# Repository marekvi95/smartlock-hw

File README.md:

# smartlock-hw

This repository contains PCB design for the **smartlock**. This project started as the final thesis at the Brno University of Technology. The aim of this project is to create a smartlock that that could be used for securing the objects.

Project is created with KiCAD version 6.0.0 nightly builds. KiCAD can be downloaded here https://kicad-pcb.org/download/

## Smartlock

Battery powered smartlock using IoT networks and NFC technology for the user authentication. Firmware source code is in this repo: https://github.com/marekvi95/smartlock-fw

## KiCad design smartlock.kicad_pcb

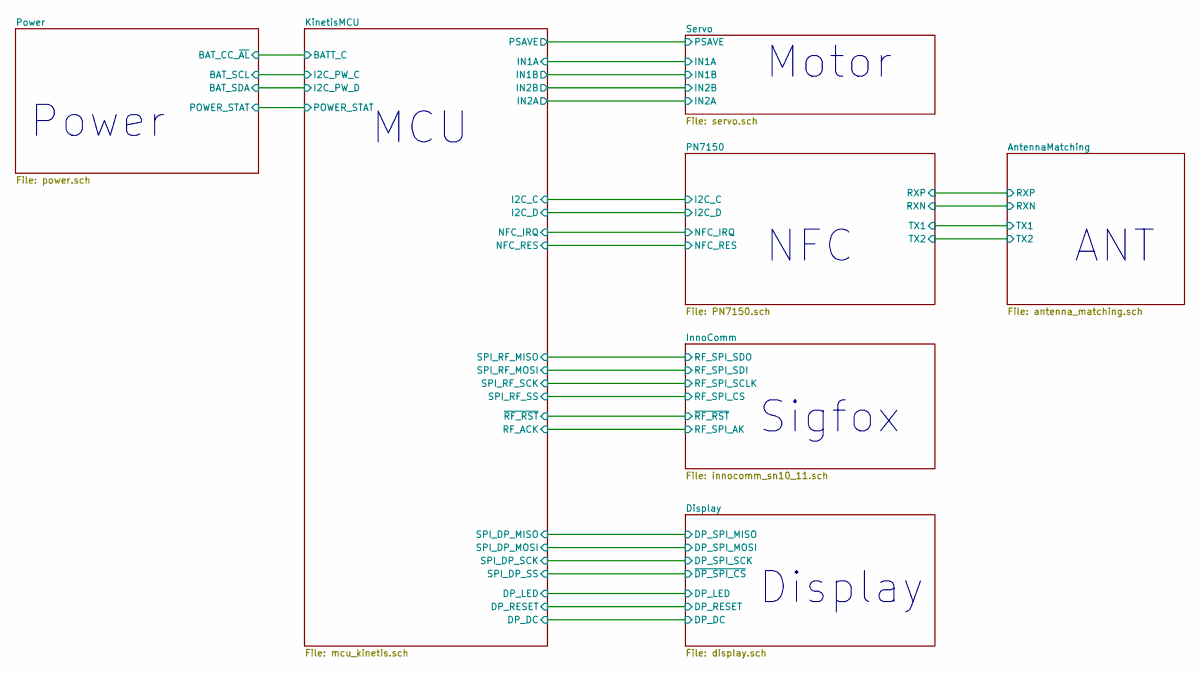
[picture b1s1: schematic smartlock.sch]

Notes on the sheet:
NFC
ANT
Sigfox
MCU
Power
Display
Motor

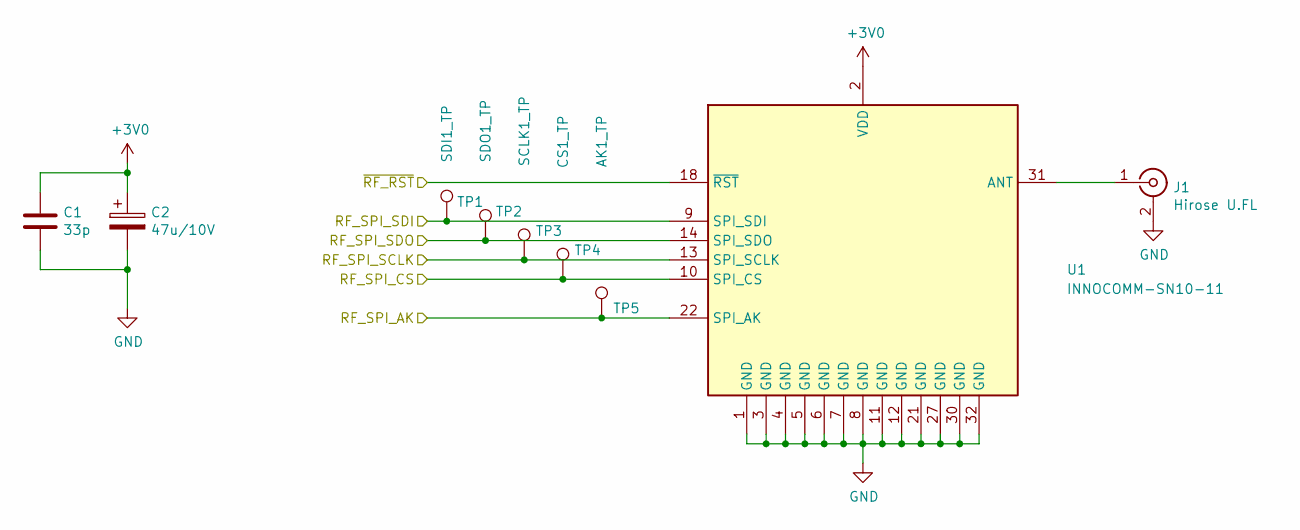
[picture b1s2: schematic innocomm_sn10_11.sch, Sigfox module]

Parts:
C1: 33p; C_0805_2012Metric
C2: 47u/10V; CP_EIA-3528-21_Kemet-B
J1: Hirose U.FL; U.FL_Hirose_U.FL-R-SMT-1_Vertical
TP1: SDI1_TP; TestPoint_Loop_D2.50mm_Drill1.0mm_LowProfile
TP2: SDO1_TP; TestPoint_Loop_D2.50mm_Drill1.0mm_LowProfile
TP3: SCLK1_TP; TestPoint_Loop_D2.50mm_Drill1.0mm_LowProfile
TP4: CS1_TP; TestPoint_Loop_D2.50mm_Drill1.0mm_LowProfile
TP5: AK1_TP; TestPoint_Loop_D2.50mm_Drill1.0mm_LowProfile
U1: INNOCOMM-SN10-11; InnoCommSN10-11

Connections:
+3V0: C1.1, C2.1, U1.2 (VDD); also elsewhere on the board
/InnoComm/RF_SPI_CS: TP4.1, U1.10 (SPI_CS); also elsewhere on the board
/InnoComm/RF_SPI_SCLK: TP3.1, U1.13 (SPI_SCLK); also elsewhere on the board
/InnoComm/RF_SPI_SDI: TP1.1, U1.9 (SPI_SDI); also elsewhere on the board
/InnoComm/RF_SPI_SDO: TP2.1, U1.14 (SPI_SDO); also elsewhere on the board
/InnoComm/~RF_RST: U1.18 (~RST); also elsewhere on the board
/KinetisMCU/RF_ACK: TP5.1, U1.22 (SPI_AK); also elsewhere on the board
GND: C1.2, C2.2, J1.2 (Ext), U1.1 (GND), U1.3 (GND), U1.4 (GND), U1.5 (GND), U1.6 (GND), U1.7 (GND), U1.8 (GND), U1.11 (GND), U1.12 (GND), U1.21 (GND), U1.27 (GND), U1.30 (GND), U1.32 (GND); also elsewhere on the board
unnamed: J1.1 (In), U1.31 (ANT)

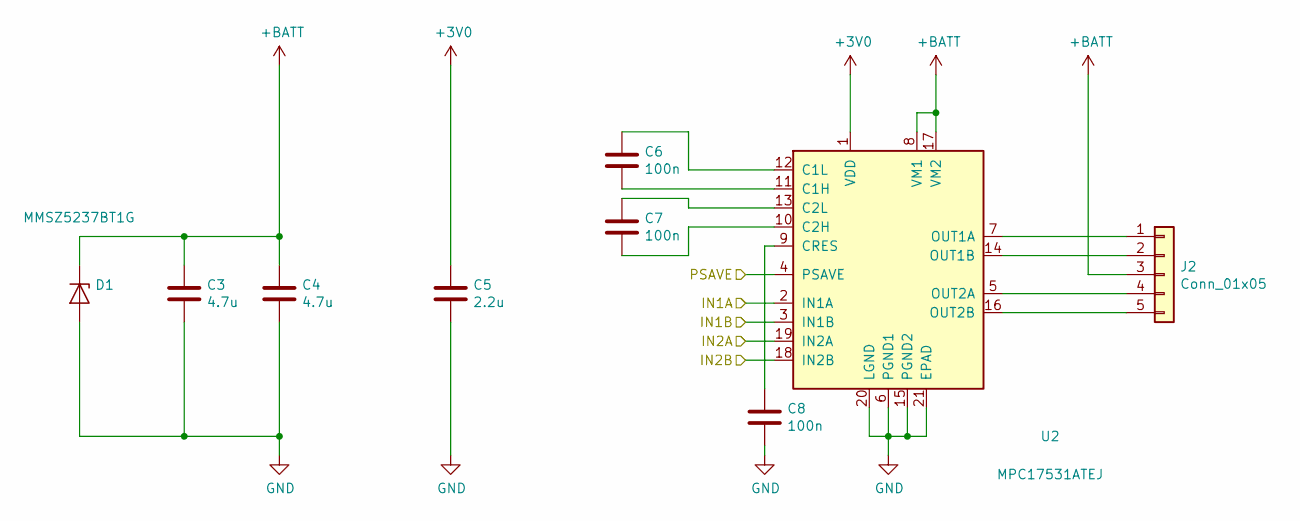
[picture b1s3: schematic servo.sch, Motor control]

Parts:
C3, C4: 4.7u; C_0805_2012Metric
C5: 2.2u; C_0805_2012Metric
C6, C7, C8: 100n; C_0805_2012Metric
D1: MMSZ5237BT1G; D_SOD-123
J2: Conn_01x05; PinHeader_1x05_P2.54mm_Vertical
U2: MPC17531ATEJ; HTSSOP-20-1EP_4.4x6.5mm_P0.65mm_EP3.4x6.5mm_ThermalVias

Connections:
+3V0: C5.1, U2.1 (VDD); also elsewhere on the board
+BATT: C3.1, C4.1, D1.1 (K), J2.3, U2.8 (VM1), U2.17 (VM2); also elsewhere on the board
/KinetisMCU/IN1A: U2.2 (IN1A); also elsewhere on the board
/KinetisMCU/IN1B: U2.3 (IN1B); also elsewhere on the board
/KinetisMCU/IN2A: U2.19 (IN2A); also elsewhere on the board
/KinetisMCU/IN2B: U2.18 (IN2B); also elsewhere on the board
/KinetisMCU/PSAVE: U2.4 (PSAVE); also elsewhere on the board
GND: C3.2, C4.2, C5.2, C8.2, D1.2 (A), U2.6 (PGND1), U2.15 (PGND2), U2.20 (LGND), U2.21 (EPAD); also elsewhere on the board
unnamed: C6.1, U2.12 (C1L)
unnamed: C6.2, U2.11 (C1H)
unnamed: C7.1, U2.13 (C2L)
unnamed: C7.2, U2.10 (C2H)
unnamed: C8.1, U2.9 (CRES)
unnamed: J2.1, U2.7 (OUT1A)
unnamed: J2.2, U2.14 (OUT1B)
unnamed: J2.4, U2.5 (OUT2A)
unnamed: J2.5, U2.16 (OUT2B)

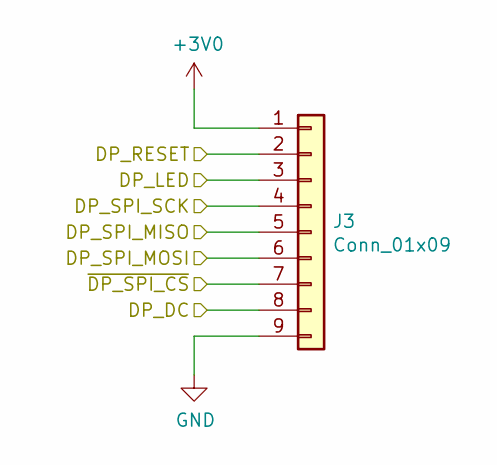
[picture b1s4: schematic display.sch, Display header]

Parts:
J3: Conn_01x09; PinHeader_1x09_P2.54mm_Vertical

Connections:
+3V0: J3.1; also elsewhere on the board
/Display/DP_DC: J3.8; also elsewhere on the board
/Display/DP_LED: J3.3; also elsewhere on the board
/Display/DP_RESET: J3.2; also elsewhere on the board
/Display/DP_SPI_MISO: J3.5; also elsewhere on the board
/Display/DP_SPI_MOSI: J3.6; also elsewhere on the board
/Display/DP_SPI_SCK: J3.4; also elsewhere on the board
/KinetisMCU/SPI_DP_SS: J3.7; also elsewhere on the board
GND: J3.9; also elsewhere on the board

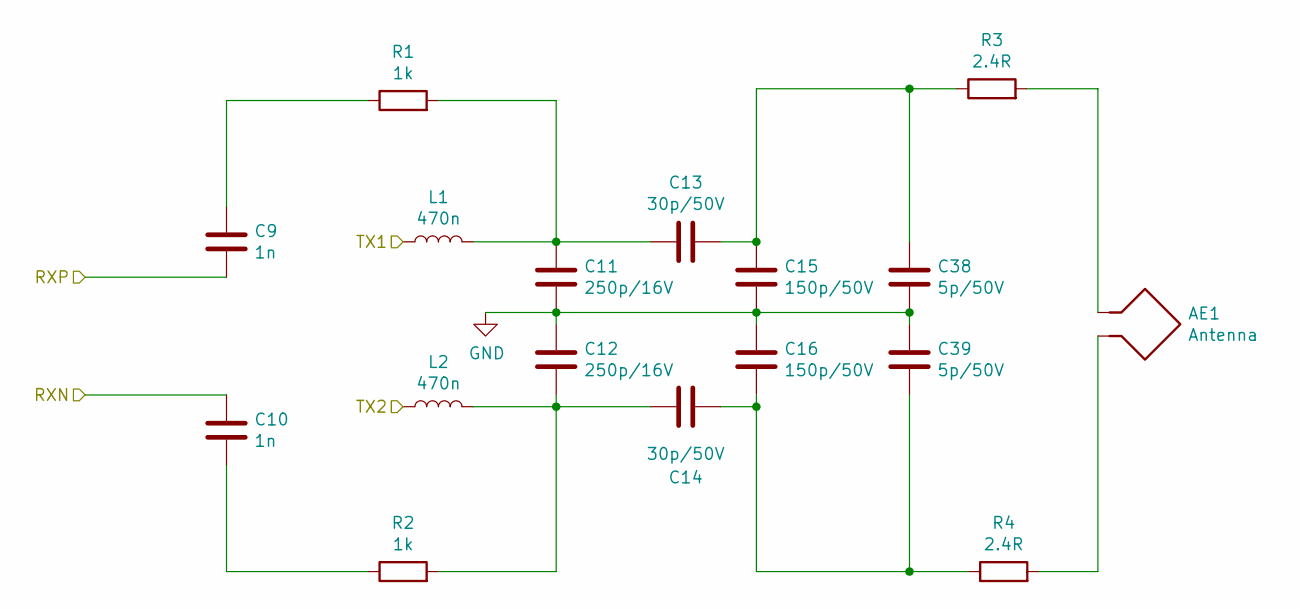
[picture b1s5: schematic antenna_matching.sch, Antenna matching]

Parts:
AE1: Antenna; nfc_40_75
C9, C10: 1n; C_0805_2012Metric
C11, C12: 250p/16V; C_0805_2012Metric
C13, C14: 30p/50V; C_0805_2012Metric
C15, C16: 150p/50V; C_0805_2012Metric
C38, C39: 5p/50V; C_0805_2012Metric
L1, L2: 470n; L_0805_2012Metric
R1, R2: 1k; R_0805_2012Metric
R3, R4: 2.4R; R_0805_2012Metric

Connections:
/AntennaMatching/RXN: C10.1; also elsewhere on the board
/AntennaMatching/RXP: C9.2; also elsewhere on the board
/AntennaMatching/TX1: L1.1; also elsewhere on the board
/AntennaMatching/TX2: L2.1; also elsewhere on the board
GND: C11.2, C12.1, C15.2, C16.1, C38.2, C39.1; also elsewhere on the board
unnamed: AE1.1, R3.2
unnamed: AE1.2, R4.2
unnamed: C9.1, R1.1
unnamed: C10.2, R2.1
unnamed: C11.1, C13.1, L1.2, R1.2
unnamed: C12.2, C14.1, L2.2, R2.2
unnamed: C13.2, C15.1, C38.1, R3.1
unnamed: C14.2, C16.2, C39.2, R4.1

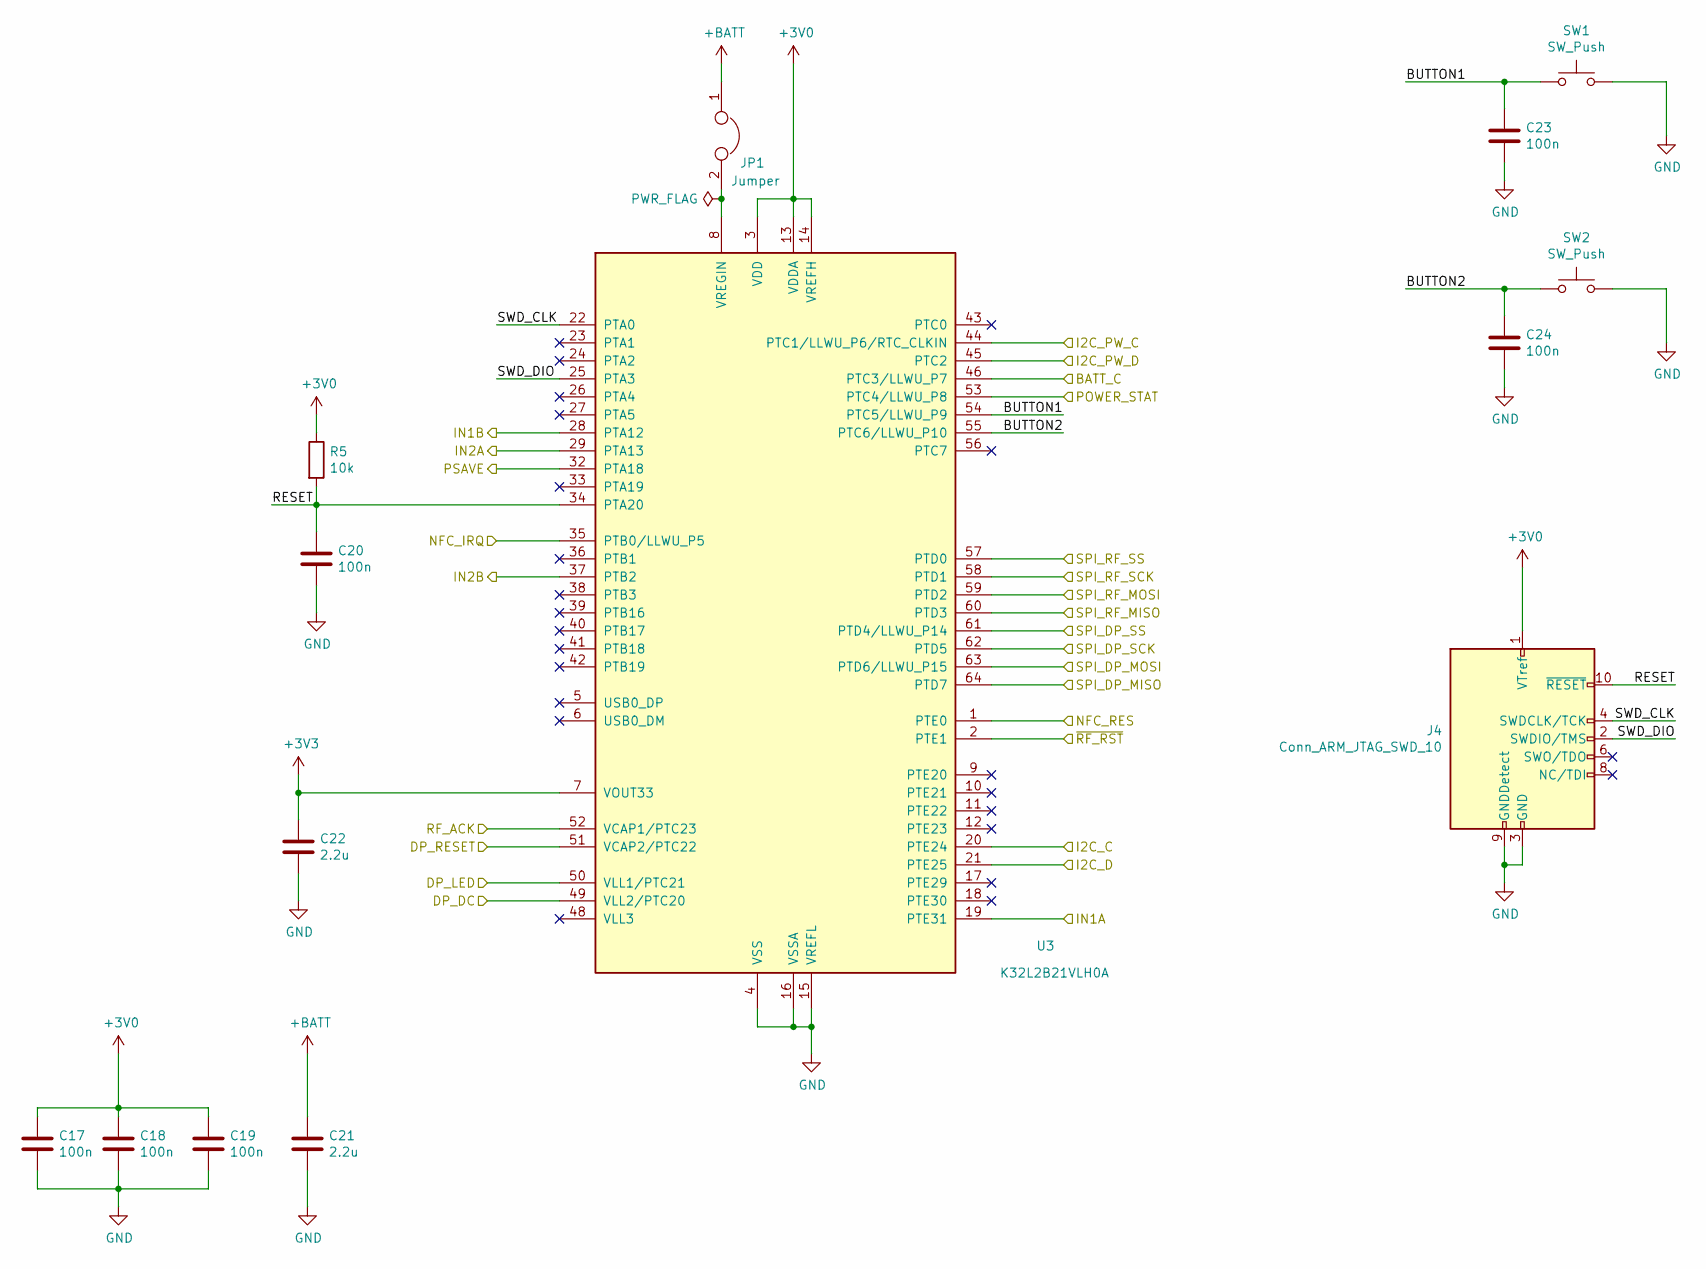
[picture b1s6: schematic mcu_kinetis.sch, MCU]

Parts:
C17, C18, C19, C20, C23, C24: 100n; C_0805_2012Metric
C21, C22: 2.2u; C_0805_2012Metric
J4: Conn_ARM_JTAG_SWD_10; PinHeader_2x05_P1.27mm_Vertical
JP1: Jumper; SolderJumper-2_P1.3mm_Bridged_Pad1.0x1.5mm
R5: 10k; R_0805_2012Metric
SW1, SW2: SW_Push; PinHeader_1x02_P1.27mm_Vertical
U3: K32L2B21VLH0A; LQFP-64_10x10mm_P0.5mm

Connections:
+3V0: C17.1, C18.1, C19.1, J4.1 (VTref), R5.1, U3.3 (VDD), U3.13 (VDDA), U3.14 (VREFH), U3.30 (VDD); also elsewhere on the board
+3V3: C22.1, U3.7 (VOUT33)
+BATT: C21.1, JP1.1; also elsewhere on the board
/Display/DP_DC: U3.49 (VLL2/PTC20); also elsewhere on the board
/Display/DP_LED: U3.50 (VLL1/PTC21); also elsewhere on the board
/Display/DP_RESET: U3.51 (VCAP2/PTC22); also elsewhere on the board
/Display/DP_SPI_MISO: U3.64 (PTD7); also elsewhere on the board
/Display/DP_SPI_MOSI: U3.63 (PTD6/LLWU_P15); also elsewhere on the board
/Display/DP_SPI_SCK: U3.62 (PTD5); also elsewhere on the board
/InnoComm/RF_SPI_CS: U3.57 (PTD0); also elsewhere on the board
/InnoComm/RF_SPI_SCLK: U3.58 (PTD1); also elsewhere on the board
/InnoComm/RF_SPI_SDI: U3.59 (PTD2); also elsewhere on the board
/InnoComm/RF_SPI_SDO: U3.60 (PTD3); also elsewhere on the board
/InnoComm/~RF_RST: U3.2 (PTE1); also elsewhere on the board
/KinetisMCU/BATT_C: U3.46 (PTC3/LLWU_P7); also elsewhere on the board
/KinetisMCU/BUTTON1: C23.1, SW1.1, U3.54 (PTC5/LLWU_P9)
/KinetisMCU/BUTTON2: C24.1, SW2.1, U3.55 (PTC6/LLWU_P10)
/KinetisMCU/I2C_C: U3.20 (PTE24); also elsewhere on the board
/KinetisMCU/I2C_D: U3.21 (PTE25); also elsewhere on the board
/KinetisMCU/IN1A: U3.19 (PTE31); also elsewhere on the board
/KinetisMCU/IN1B: U3.28 (PTA12); also elsewhere on the board
/KinetisMCU/IN2A: U3.29 (PTA13); also elsewhere on the board
/KinetisMCU/IN2B: U3.37 (PTB2); also elsewhere on the board
/KinetisMCU/NFC_IRQ: U3.35 (PTB0/LLWU_P5); also elsewhere on the board
/KinetisMCU/NFC_RES: U3.1 (PTE0); also elsewhere on the board
/KinetisMCU/POWER_STAT: U3.53 (PTC4/LLWU_P8); also elsewhere on the board
/KinetisMCU/PSAVE: U3.32 (PTA18); also elsewhere on the board
/KinetisMCU/RESET: C20.1, J4.10 (~RESET~), R5.2, U3.34 (PTA20)
/KinetisMCU/RF_ACK: U3.52 (VCAP1/PTC23); also elsewhere on the board
/KinetisMCU/SPI_DP_SS: U3.61 (PTD4/LLWU_P14); also elsewhere on the board
/KinetisMCU/SWD_CLK: J4.4 (SWDCLK/TCK), U3.22 (PTA0)
/KinetisMCU/SWD_DIO: J4.2 (SWDIO/TMS), U3.25 (PTA3)
/Power/BAT_SCL: U3.44 (PTC1/LLWU_P6/RTC_CLKIN); also elsewhere on the board
/Power/BAT_SDA: U3.45 (PTC2); also elsewhere on the board
GND: C17.2, C18.2, C19.2, C20.2, C21.2, C22.2, C23.2, C24.2, J4.3 (GND), J4.5 (GND), J4.9 (GNDDetect), SW1.2, SW2.2, U3.4 (VSS), U3.15 (VREFL), U3.16 (VSSA), U3.31 (VSS), U3.47 (VSS); also elsewhere on the board
unnamed: JP1.2, U3.8 (VREGIN)

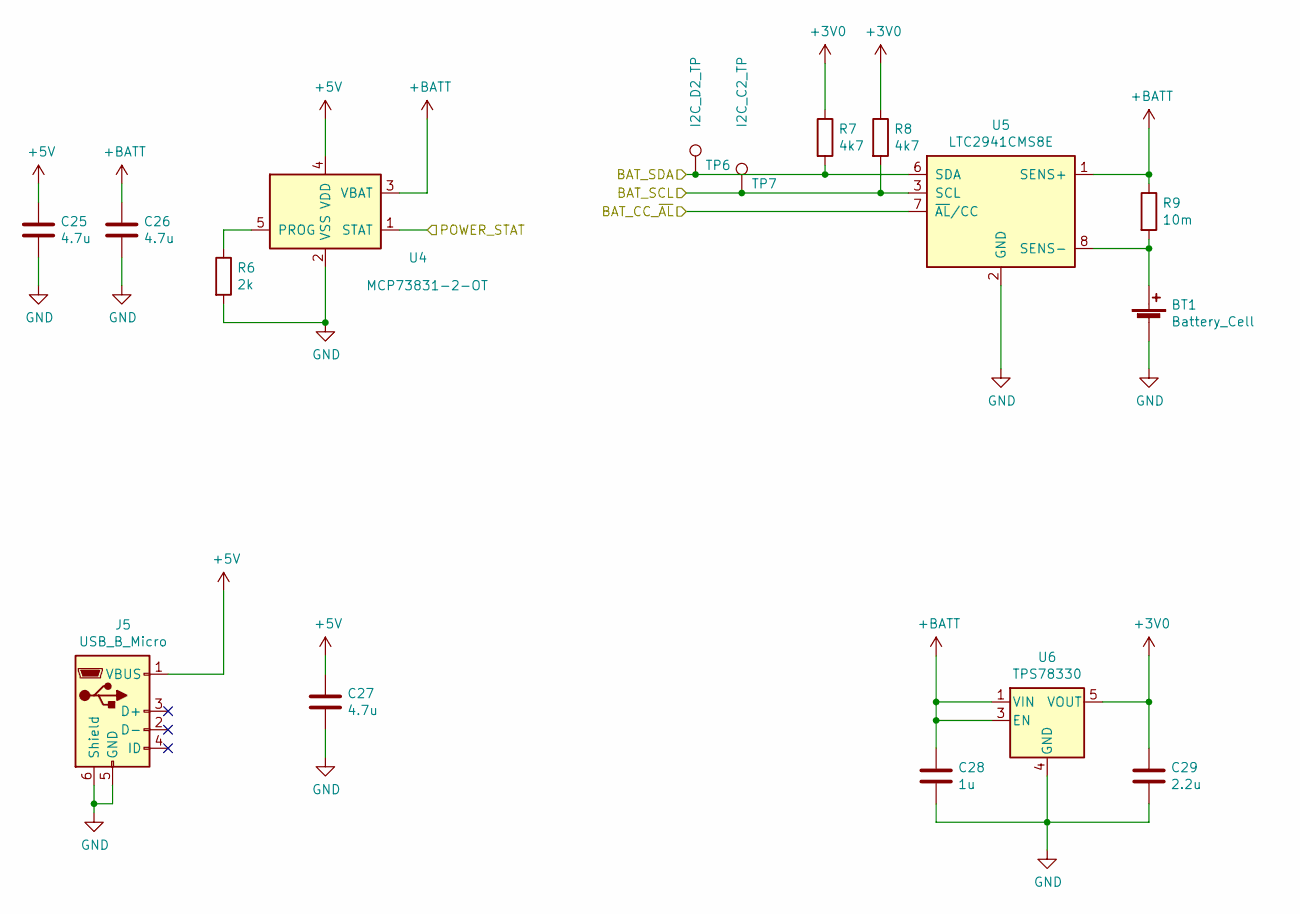
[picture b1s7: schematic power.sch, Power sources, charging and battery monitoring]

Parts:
BT1: Battery_Cell; BatteryHolder_MPD_BH-18650-PC2
C25, C26, C27: 4.7u; C_0805_2012Metric
C28: 1u; C_0805_2012Metric
C29: 2.2u; C_0805_2012Metric
J5: USB_B_Micro; USB_Micro-B_Molex_47346-0001
R6: 2k; R_0805_2012Metric
R7, R8: 4k7; R_0805_2012Metric
R9: 10m; R_0805_2012Metric
TP6: I2C_D2_TP; TestPoint_Loop_D2.50mm_Drill1.0mm_LowProfile
TP7: I2C_C2_TP; TestPoint_Loop_D2.50mm_Drill1.0mm_LowProfile
U4: MCP73831-2-OT; SOT-23-5
U5: LTC2941CMS8E; MSOP-8-1EP_3x3mm_P0.65mm_EP1.68x1.88mm
U6: TPS78330; SOT-23-5

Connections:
+3V0: C29.1, R7.1, R8.1, U6.5 (VOUT); also elsewhere on the board
+5V: C25.1, C27.1, J5.1 (VBUS), U4.4 (VDD)
+BATT: C26.1, C28.1, R9.1, U4.3 (VBAT), U5.1 (SENS+), U6.1 (VIN), U6.3 (EN); also elsewhere on the board
/KinetisMCU/BATT_C: U5.7 (~AL~/CC); also elsewhere on the board
/KinetisMCU/POWER_STAT: U4.1 (STAT); also elsewhere on the board
/Power/BAT_SCL: R8.2, TP7.1, U5.3 (SCL); also elsewhere on the board
/Power/BAT_SDA: R7.2, TP6.1, U5.6 (SDA); also elsewhere on the board
GND: BT1.2 (-), C25.2, C26.2, C27.2, C28.2, C29.2, J5.5 (GND), J5.6 (Shield), R6.2, U4.2 (VSS), U5.2 (GND), U6.2 (GND), U6.4 (GND); also elsewhere on the board
unnamed: BT1.1 (+), R9.2, U5.8 (SENS-)
unnamed: R6.1, U4.5 (PROG)

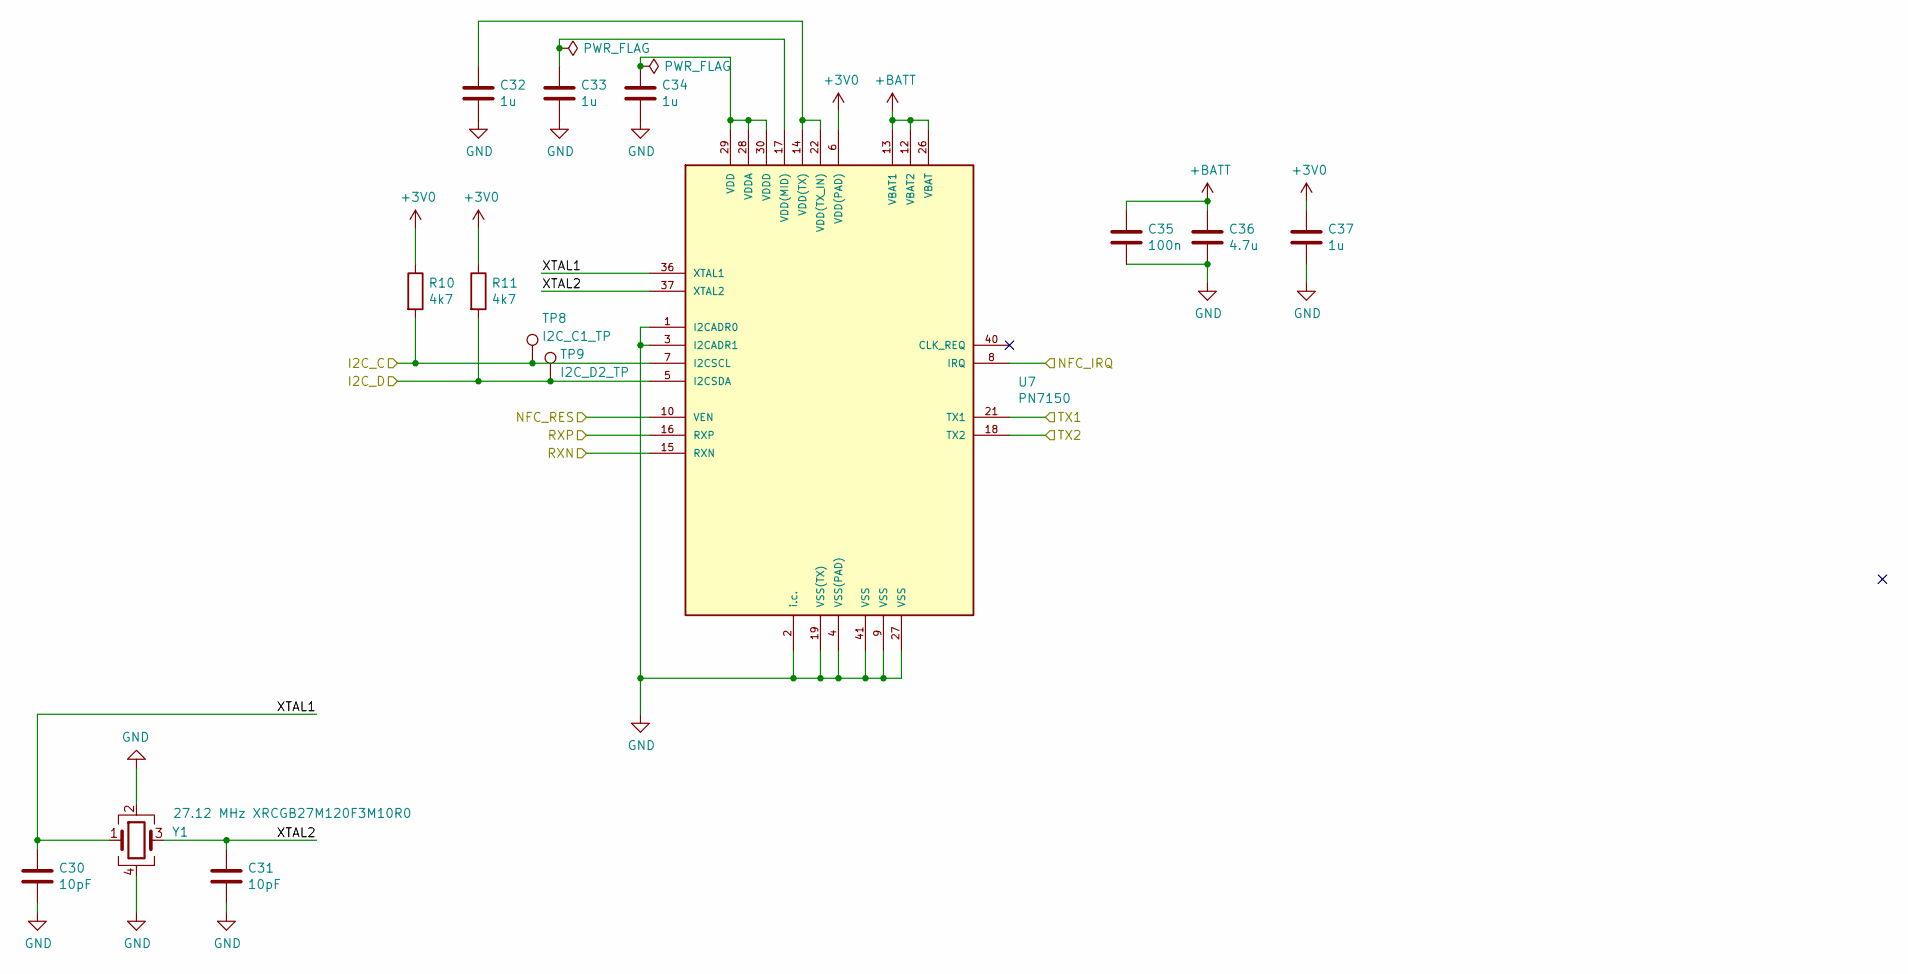
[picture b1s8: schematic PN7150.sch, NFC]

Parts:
C30, C31: 10pF; C_0805_2012Metric
C32, C33, C34, C37: 1u; C_0805_2012Metric
C35: 100n; C_0805_2012Metric
C36: 4.7u; C_0805_2012Metric
R10, R11: 4k7; R_0805_2012Metric
TP8: I2C_C1_TP; TestPoint_Loop_D2.50mm_Drill1.0mm_LowProfile
TP9: I2C_D2_TP; TestPoint_Loop_D2.50mm_Drill1.0mm_LowProfile
U7: PN7150; QFN-40-1EP_6x6mm_P0.5mm_EP4.6x4.6mm
Y1: 27.12 MHz XRCGB27M120F3M10R0; Crystal_SMD_2016-4Pin_2.0x1.6mm

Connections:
+3V0: C37.1, R10.1, R11.1, U7.6 (VDD(PAD)); also elsewhere on the board
+BATT: C35.1, C36.1, U7.12 (VBAT2), U7.13 (VBAT1), U7.26 (VBAT); also elsewhere on the board
/AntennaMatching/RXN: U7.15 (RXN); also elsewhere on the board
/AntennaMatching/RXP: U7.16 (RXP); also elsewhere on the board
/AntennaMatching/TX1: U7.21 (TX1); also elsewhere on the board
/AntennaMatching/TX2: U7.18 (TX2); also elsewhere on the board
/KinetisMCU/I2C_C: R10.2, TP8.1, U7.7 (I2CSCL); also elsewhere on the board
/KinetisMCU/I2C_D: R11.2, TP9.1, U7.5 (I2CSDA); also elsewhere on the board
/KinetisMCU/NFC_IRQ: U7.8 (IRQ); also elsewhere on the board
/KinetisMCU/NFC_RES: U7.10 (VEN); also elsewhere on the board
/PN7150/XTAL1: C30.1, U7.36 (XTAL1), Y1.1
/PN7150/XTAL2: C31.1, U7.37 (XTAL2), Y1.3
GND: C30.2, C31.2, C32.2, C33.2, C34.2, C35.2, C36.2, C37.2, U7.1 (I2CADR0), U7.2 (i.c.), U7.3 (I2CADR1), U7.4 (VSS(PAD)), U7.9 (VSS), U7.19 (VSS(TX)), U7.27 (VSS), U7.41 (VSS), Y1.2, Y1.4; also elsewhere on the board
unnamed: C32.1, U7.14 (VDD(TX)), U7.22 (VDD(TX_IN))
unnamed: C33.1, U7.17 (VDD(MID))
unnamed: C34.1, U7.28 (VDDA), U7.29 (VDD), U7.30 (VDDD)

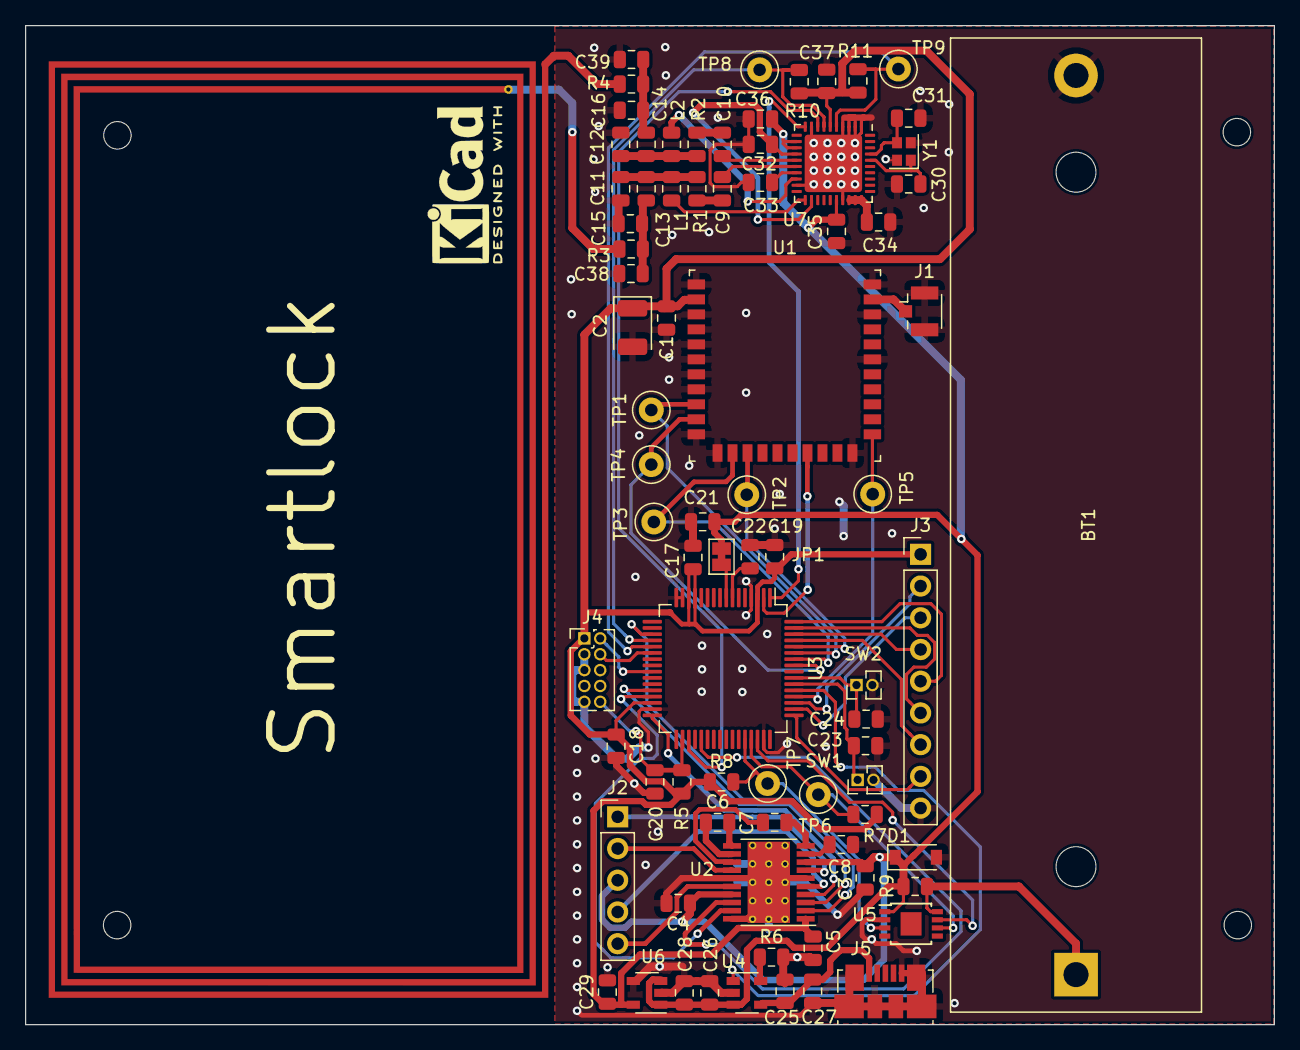
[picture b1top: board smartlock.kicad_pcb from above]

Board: 2 copper layers, 100.0 x 80.0 mm, 80 parts (0 on the bottom side), 66 nets.

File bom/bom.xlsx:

Source: | C:\Users\nxf46245\Documents\github\diplomka\schema.sch
Date: | 43807.717349537037
Tool: | Eeschema (5.1.2)-1
Generator: | C:\Program Files\KiCad\bin\scripting\plugins/bom_csv_grouped_by_value_with_fp.py |  |  |  |  |  | Part number | URL | Cena | Nazev | Vyribce
Component Count: | 78
Ref | Qnty | Value | Cmp name | Footprint | Description | Vendor
AE1, | 1 | Antenna | Antenna_Loop | Antenna:nfc_40_75 | Loop antenna
BT1, | 1 | Battery_Cell | Battery_Cell | Battery:BatteryHolder_MPD_BH-18650-PC2 | Single-cell battery |  | BK-18650-PC2 | https://www.digikey.com/product-detail/en/mpd-memory-protect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 | 70 |  | Memory protection devices
C1, | 1 | 33p | C | Capacitor_SMD:C_0805_2012Metric | Unpolarized capacitor |  | C0805C330K5HACAUTO |  | 3,51 |  | Kemet
C2, | 1 | 47u 10V | CP | Capacitor_Tantalum_SMD:CP_EIA-3528-21_Kemet-B | Polarized capacitor |  | TPSB476M010T0250
C4, C3, C27, C25, C26, | 5 | 4.7u | C | Capacitor_SMD:C_0805_2012Metric | Unpolarized capacitor |  | C0805C475K8PACTU |  | 3,98 |  | KEMET | Vícevrstvé keramické kondenzátory MLCC – pro povrchovou montáž SMD, SMT 4.7UF 1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
C5, C22, C21, C29, | 4 | 2.2u | C | Capacitor_SMD:C_0805_2012Metric | Unpolarized capacitor |  | C0805C225K8RACTU |  | 3,74 |  | KEMET | Vícevrstvé keramické kondenzátory MLCC – pro povrchovou montáž SMD, SMT 2.2UF 1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
C7, C8, C6, C17, C18, C19, C20, C24, C23, C35, | 10 | 100n | C | Capacitor_SMD:C_0805_2012Metric | Unpolarized capacitor |  | C0805C104K8RACTU |  | 4,91 |  | KEMET | Vícevrstvé keramické kondenzátory MLCC – pro povrchovou montáž SMD, SMT 10V 0.1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
C10, C9, | 2 | 1nF | C | Capacitor_SMD:C_0805_2012Metric | Unpolarized capacitor |  | C0805C102J5GAC7210 |  | 3,04 |  | KEMET | Vícevrstvé keramické kondenzátory MLCC – pro povrchovou montáž SMD, SMT 50V 100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
C11, C12, | 2 | 250pF/16V | C | Capacitor_SMD:C_0805_2012Metric | Unpolarized capacitor |  | 08055A251JAT2A |  | 6.79 |  | AVX | Vícevrstvé keramické kondenzátory MLCC – pro povrchovou montáž SMD, SMT 50V 250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
C13, C14, | 2 | 30p/50V | C | Capacitor_SMD:C_0805_2012Metric | Unpolarized capacitor |  | 08055A300GAT2A |  | 11 |  | AVX | Vícevrstvé keramické kondenzátory MLCC – pro povrchovou montáž SMD, SMT 50V 30 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
C15, C16, | 2 | 155pF/50V | C | Capacitor_SMD:C_0805_2012Metric | Unpolarized capacitor |  | 08055A151FAT2A |  | 7.96 |  | AVX
C28, | 1 | 1u | C | Capacitor_SMD:C_0805_2012Metric | Unpolarized capacitor |  | C0805C105K8RACTU |  | 2,57 |  | KEMET
C30, C31, | 2 | 10pF | C | Capacitor_SMD:C_0805_2012Metric | Unpolarized capacitor |  | SQCFVA100JATME |  | 21,76 |  | AVX | Vícevrstvé keramické kondenzátory MLCC – pro povrchovou montáž SMD, SMT 250V 10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
C34, C37, C33, C32, | 4 | 1uF | C | Capacitor_SMD:C_0805_2012Metric | Unpolarized capacitor |  | C0805C105K8RACTU |  | 2,57 |  | KEMET | Vícevrstvé keramické kondenzátory MLCC – pro povrchovou montáž SMD, SMT 10V 1uF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
C36, | 1 | 4.7uF | C | Capacitor_SMD:C_0805_2012Metric | Unpolarized capacitor |  | C0805C475K8PACTU |  | 3,98 |  | KEMET | Vícevrstvé keramické kondenzátory MLCC – pro povrchovou montáž SMD, SMT 4.7UF 1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
D1, | 1 | MMSZ5237BT1G | D_Zener | Diode_SMD:D_SOD-123 | Zener diode |  | MMSZ5237BT1G |  | 4,68 |  | ON Semiconductor | Zenerovy diody 8.2V 500mW
J1, | 1 | Conn_Coaxial | Conn_Coaxial | Connector_Coaxial:U.FL_Hirose_U.FL-R-SMT-1_Vertical | coaxial connector (BNC, SMA, SMB, SMC, Cinch/RCA, ...) |  | U.FL-R-SMT-1(10) |  | 27,82 |  | Hirose connector | VF koaxiální konektory SMT ML REC AU 50 OHM W/ANTI SLDR WCKNG RL
J2, | 1 | Conn_01x05 | Conn_01x05 | Connector_PinHeader_2.54mm:PinHeader_1x05_P2.54mm_Vertical | Generic connector, single row, 01x05, script generated (kicad-library-utils/sch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
J3, | 1 | Conn_01x09 | Conn_01x09 | Connector_PinHeader_2.54mm:PinHeader_1x09_P2.54mm_Vertical | Generic connector, single row, 01x09, script generated (kicad-library-utils/sch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
J4, | 1 | Conn_ARM_JTAG_SWD_10 | Conn_ARM_JTAG_SWD_10 | Connector_PinHeader_1.27mm:PinHeader_2x05_P1.27mm_Vertical | Cortex Debug Connector, standard ARM Cortex-M SWD and JTAG interface
J5, | 1 | USB_B_Micro | USB_B_Micro | Connector_USB:USB_Micro-B_Molex_47346-0001 | USB Micro Type B connector
JP1, | 1 | Jumper | Jumper | Jumper:SolderJumper-2_P1.3mm_Bridged_Pad1.0x1.5mm | Jumper, normally closed
L1, L2, | 2 | 470n | L | Inductor_SMD:L_0805_2012Metric | Inductor |  | LQM21NNR47K10D |  | 5,15 Kč |  | Murata | Pevné cívky 0805 0.47uH 10%
R1, R2, | 2 | 1k | R | Resistor_SMD:R_0805_2012Metric | Resistor |  | RT0805FRE101KL |  | 2,81 |  | Yageo | Tenkovrstvé rezistory - SMD 1K ohm 1% 50 ppm Thin Film
R3, R4, | 2 | 2 | R | Resistor_SMD:R_0805_2012Metric | Resistor
R5, | 1 | 10k | R | Resistor_SMD:R_0805_2012Metric | Resistor
R6, | 1 | 2k | R | Resistor_SMD:R_0805_2012Metric | Resistor |  | RT0805FRE072KL |  | 2,81 |  | Yageo | Tenkovrstvé rezistory - SMD 1/8W 2K ohm 1% 50ppm
R8, R7, R10, R11, | 4 | 4k7 | R | Resistor_SMD:R_0805_2012Metric | Resistor |  | RT0805FRE134K7L |  | 2,81 |  | Yageo |  | Tenkovrstvé rezistory - SMD 4.7K ohm 1% 50 ppm Thin Film
R9, | 1 | 10m | R | Resistor_SMD:R_0805_2012Metric | Resistor |  | TLR2BDTD12L0F75 |  | 16,48 |  | KOA | Rezistory ke snímání proudu - SMD 2W 12 mOhm 1%
SW1, SW2, | 2 | SW_Push | SW_Push | Connector_PinHeader_1.27mm:PinHeader_1x02_P1.27mm_Vertical | Push button switch, generic, two pins
TP1, | 1 | SDI1_TP | TestPoint | TestPoint:TestPoint_Loop_D2.50mm_Drill1.0mm_LowProfile | test point
TP2, | 1 | SDO1_TP | TestPoint | TestPoint:TestPoint_Loop_D2.50mm_Drill1.0mm_LowProfile | test point
TP3, | 1 | SCLK1_TP | TestPoint | TestPoint:TestPoint_Loop_D2.50mm_Drill1.0mm_LowProfile | test point
TP4, | 1 | CS1_TP | TestPoint | TestPoint:TestPoint_Loop_D2.50mm_Drill1.0mm_LowProfile | test point
TP5, | 1 | AK1_TP | TestPoint | TestPoint:TestPoint_Loop_D2.50mm_Drill1.0mm_LowProfile | test point
TP6, TP9, | 2 | I2C_D2_TP | TestPoint | TestPoint:TestPoint_Loop_D2.50mm_Drill1.0mm_LowProfile | test point
TP7, | 1 | I2C_C2_TP | TestPoint | TestPoint:TestPoint_Loop_D2.50mm_Drill1.0mm_LowProfile | test point
TP8, | 1 | I2C_C1_TP | TestPoint | TestPoint:TestPoint_Loop_D2.50mm_Drill1.0mm_LowProfile | test point
U1, | 1 | INNOCOMM-SN10-11 | INNOCOMM-SN10-11 | Antenna:InnoCommSN10-11 | InnoComm SN10-11 Sigfox module
U2, | 1 | MPC17531ATEJ | MPC17531ATEJ | Package_SO:HTSSOP-20-1EP_4.4x6.5mm_P0.65mm_EP3.4x6.5mm_ThermalVias | 700 mA dual H-Bridge motor driver with 3.0 V compatible logic I/O |  | MPC17531ATEJ |  | 58,50 |  | NXP | Motorové / Pohyblivé / Zážehové ovladače a mechanismy H-Bridge, Dual, Low Volta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
U3, | 1 | K32L2B21VLH0A | K32L2B21VLH0A | Package_QFP:LQFP-64_10x10mm_P0.5mm | Kinetis KL32L2B series, 48-MHz/32-bit ARM Cortex-M0+, 128kB flash, 32 kB SRAM, 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 |  | K32L2B21VLH0A |  | 94,12 |  | NXP | Mikrořadiče ARM – MCU K32 L2B, 64LQFP
U4, | 1 | MCP73831-2-OT | MCP73831-2-OT | Package_TO_SOT_SMD:SOT-23-5 | Single cell, Li-Ion/Li-Po charge management controller, 4.20V, Tri-State Status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 |  | MCP73831T-3ACI/OT |  | 13,10 |  | Microchip | Řízení baterie Charge mgnt contr
U5, | 1 | LTC2941CMS8E | LTC2941CMS8E | Package_SO:MSOP-8-1EP_3x3mm_P0.65mm_EP1.68x1.88mm | Battery Gas Gauge with I2C Interface |  | LTC2941CMS8E#PBF |  | 76,18 |  | Analog Devices | Řízení baterie Battery Gas Gauge w/ I2C
U6, | 1 | TPS78330 | TPS78330 | Package_TO_SOT_SMD:SOT-23-5 | Ultralow Quiescent Current 150mA LDO, 3.0V fixed output voltage, SOT-23-5 |  | TPS78330DDCR |  | 21,29 |  | TI | Regulátory napětí s nízkým úbytkem (LDO) 150mA Ultra-Lo Quies Crnt Iq0.5uA LDO 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
U7, | 1 | PN7150 | PN7150 | Package_DFN_QFN:QFN-40-1EP_6x6mm_P0.5mm_EP4.6x4.6mm_ThermalVias | PN7120 - Full NFC Forum-compliant controller with integrated firmware and NCI i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 |  | PN7150B0HN/C11004Y |  | 156,78 |  | NXP | Transpondéry RFID High performance NFC controller, supporting all NFC Forum mod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
Y1, | 1 | 27.12 MHz XRCGB27M120F3M10R0 | Crystal_GND24 | Crystal:Crystal_SMD_2016-4Pin_2.0x1.6mm | Four pin crystal, GND on pins 2 and 4

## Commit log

2020-04-04 added readme

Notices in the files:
PN7150.sch:
License: BSD 3-clause
